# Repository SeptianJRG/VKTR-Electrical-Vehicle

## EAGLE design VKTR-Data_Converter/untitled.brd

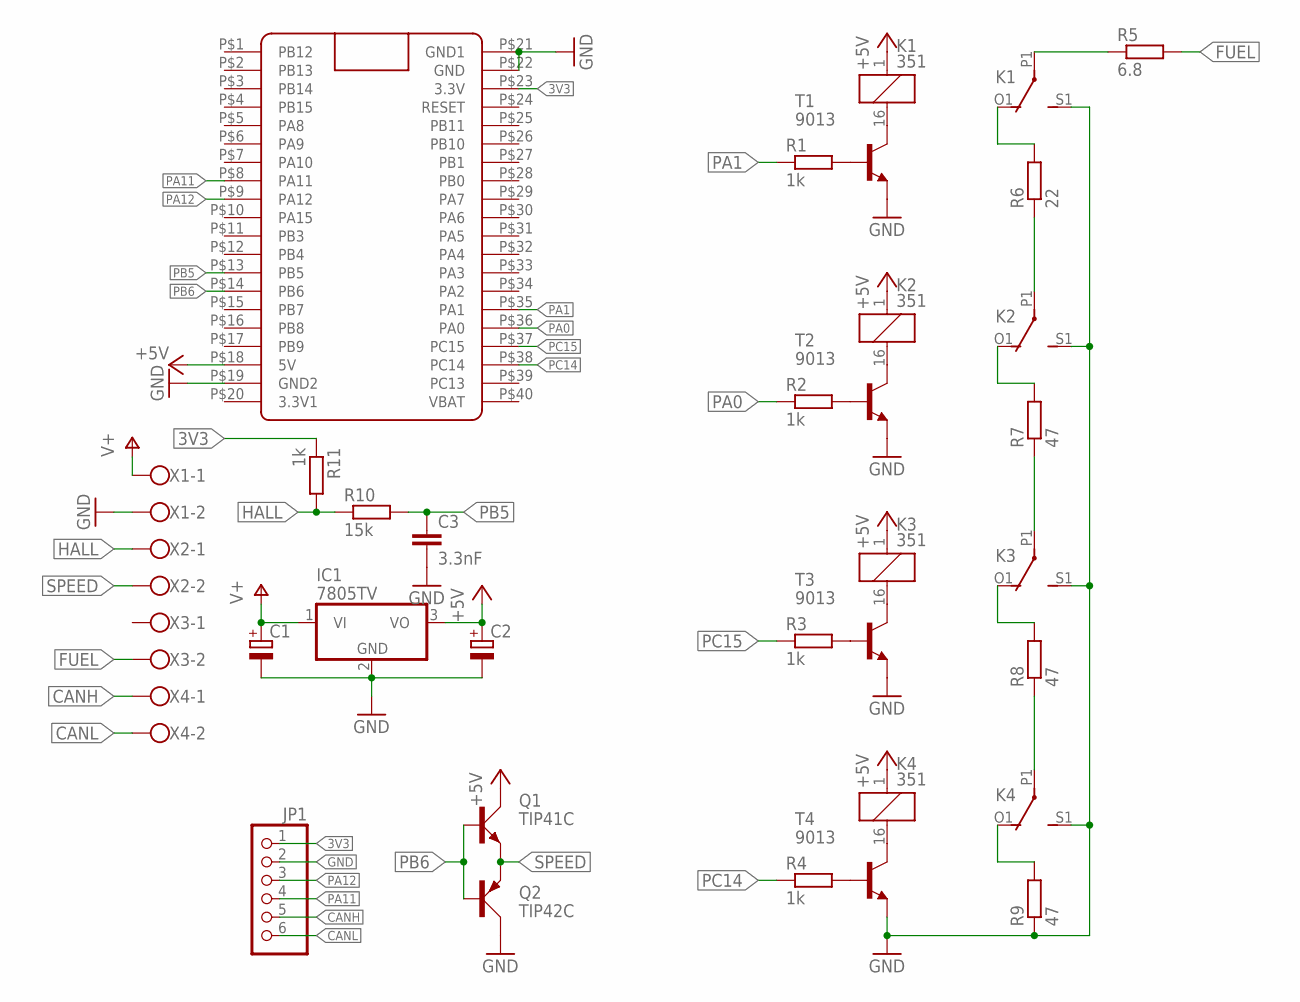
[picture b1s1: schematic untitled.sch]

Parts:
C1, C2: CPOL-EUE5-10.5; E5-10,5
C3: 3.3nF; C050-024X044
IC1: 7805TV; TO220V
JP1: PINHD-1X6; 1X06
K1, K2, K3, K4: 351
Q1: TIP41C; TO220AV
Q2: TIP42C; TO220AV
R1, R2, R3, R4, R11: 1k; 0207/7
R5: 6.8; 0207/7
R6: 22; 0207/7
R7, R8, R9: 47; 0207/7
R10: 15k; 0207/7
T1, T2, T3, T4: 9013; TO92-EBC
U$1: BLUE_PILL
X1, X2, X3, X4: W237-102

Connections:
3V3: JP1.1, R11.1, U$1.P$23 (3.3V)
+5V: C2.+, IC1.3 (VO), K1.1, K2.1, K3.1, K4.1, Q1.C, U$1.P$18 (5V)
CANH: JP1.5, X4.1
CANL: JP1.6, X4.2
FUEL: R5.2, X3.2
GND: C1.-, C2.-, C3.2, IC1.2 (GND), JP1.2, K1.S1 (S), K2.S1 (S), K3.S1 (S), K4.S1 (S), Q2.C, R9.1, T1.E, T2.E, T3.E, T4.E, U$1.P$19 (GND2), U$1.P$21 (GND1), U$1.P$22 (GND), X1.2
HALL: R10.1, R11.2, X2.1
unnamed: K1.P1, R5.1
unnamed: K1.16 (2), T1.C
unnamed: R1.2, T1.B
unnamed: K2.16 (2), T2.C
unnamed: R2.2, T2.B
unnamed: K3.16 (2), T3.C
unnamed: R3.2, T3.B
unnamed: K4.16 (2), T4.C
unnamed: R4.2, T4.B
unnamed: K2.P1, R6.1
unnamed: K1.O1 (O), R6.2
unnamed: K3.P1, R7.1
unnamed: K2.O1 (O), R7.2
unnamed: K4.P1, R8.1
unnamed: K3.O1 (O), R8.2
unnamed: K4.O1 (O), R9.2
PA0: R2.1, U$1.P$36 (PA0)
PA1: R1.1, U$1.P$35 (PA1)
PA11: JP1.4, U$1.P$8 (PA11)
PA12: JP1.3, U$1.P$9 (PA12)
PB5: C3.1, R10.2, U$1.P$13 (PB5)
PB6: Q1.B, Q2.B, U$1.P$14 (PB6)
PC14: R4.1, U$1.P$38 (PC14)
PC15: R3.1, U$1.P$37 (PC15)
SPEED: Q1.E, Q2.E, X2.2
V+: C1.+, IC1.1 (VI), X1.1

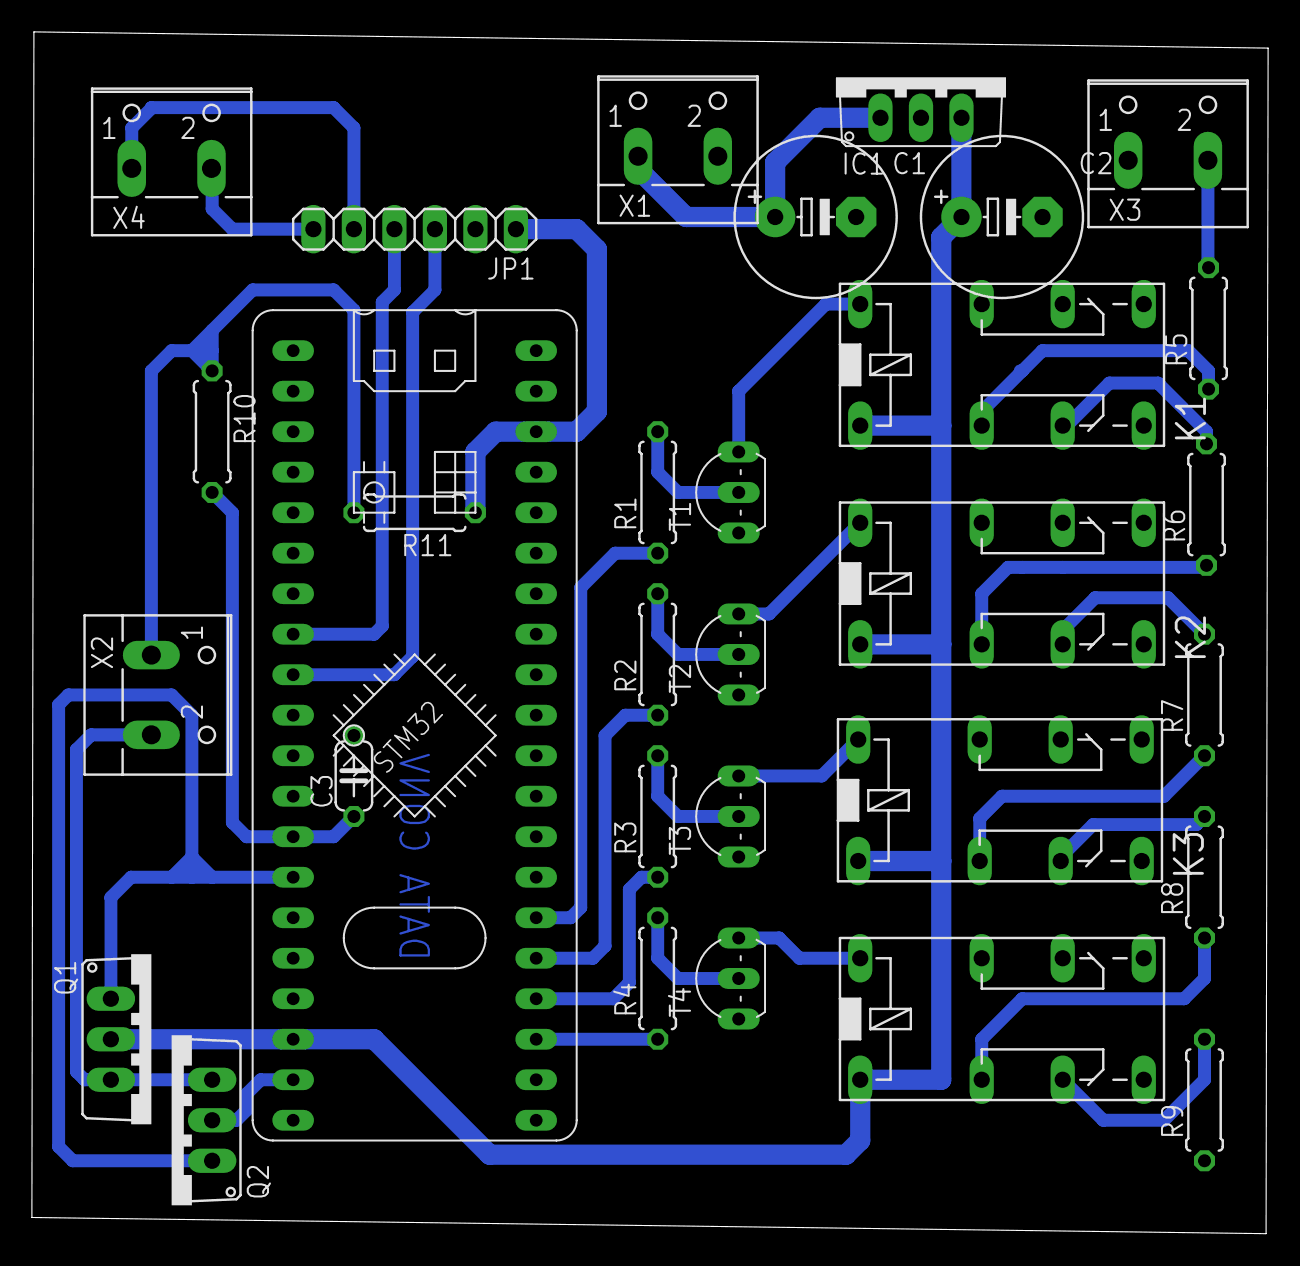
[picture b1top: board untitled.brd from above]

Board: 2 copper layers, 77.5 x 75.4 mm, 31 parts (0 on the bottom side), 33 nets.

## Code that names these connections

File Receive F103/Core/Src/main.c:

/* USER CODE BEGIN Header */
/**
  ******************************************************************************
  * @file           : main.c
  * @brief          : Main program body
  ******************************************************************************
  * @attention
  *
  * Copyright (c) 2022 STMicroelectronics.
  * All rights reserved.
  *
  * This software is licensed under terms that can be found in the LICENSE file
  * in the root directory of this software component.
  * If no LICENSE file comes with this software, it is provided AS-IS.
  *
  ******************************************************************************
  */
/* USER CODE END Header */
/* Includes ------------------------------------------------------------------*/
#include "main.h"

/* Private includes ----------------------------------------------------------*/
/* USER CODE BEGIN Includes */

/* USER CODE END Includes */

/* Private typedef -----------------------------------------------------------*/
/* USER CODE BEGIN PTD */

/* USER CODE END PTD */

/* Private define ------------------------------------------------------------*/
/* USER CODE BEGIN PD */
/* USER CODE END PD */

/* Private macro -------------------------------------------------------------*/
/* USER CODE BEGIN PM */

/* USER CODE END PM */

/* Private variables ---------------------------------------------------------*/

/* USER CODE BEGIN PV */

/* USER CODE END PV */

/* Private function prototypes -----------------------------------------------*/
void SystemClock_Config(void);
static void MX_GPIO_Init(void);
/* USER CODE BEGIN PFP */

/* USER CODE END PFP */

/* Private user code ---------------------------------------------------------*/
/* USER CODE BEGIN 0 */

/* USER CODE END 0 */

/**
  * @brief  The application entry point.
  * @retval int
  */
int main(void)
{
  /* USER CODE BEGIN 1 */

  /* USER CODE END 1 */

  /* MCU Configuration--------------------------------------------------------*/

  /* Reset of all peripherals, Initializes the Flash interface and the Systick. */
  HAL_Init();

  /* USER CODE BEGIN Init */

  /* USER CODE END Init */

  /* Configure the system clock */
  SystemClock_Config();

  /* USER CODE BEGIN SysInit */

  /* USER CODE END SysInit */

  /* Initialize all configured peripherals */
  MX_GPIO_Init();
  /* USER CODE BEGIN 2 */

  /* USER CODE END 2 */

  /* Infinite loop */
  /* USER CODE BEGIN WHILE */
  while (1)
  {
    /* USER CODE END WHILE */

    /* USER CODE BEGIN 3 */
		HAL_GPIO_WritePin(GPIOC, GPIO_PIN_14, 1);
		HAL_GPIO_WritePin(GPIOC, GPIO_PIN_15, 0);
		HAL_GPIO_WritePin(GPIOA, GPIO_PIN_0, 0);
		HAL_GPIO_WritePin(GPIOA, GPIO_PIN_1, 0);

		HAL_Delay(1000);

		HAL_GPIO_WritePin(GPIOC, GPIO_PIN_14, 0);
		HAL_GPIO_WritePin(GPIOC, GPIO_PIN_15, 1);
		HAL_GPIO_WritePin(GPIOA, GPIO_PIN_0, 0);
		HAL_GPIO_WritePin(GPIOA, GPIO_PIN_1, 0);

		HAL_Delay(1000);
		
		HAL_GPIO_WritePin(GPIOC, GPIO_PIN_14, 0);
		HAL_GPIO_WritePin(GPIOC, GPIO_PIN_15, 0);
		HAL_GPIO_WritePin(GPIOA, GPIO_PIN_0, 1);
		HAL_GPIO_WritePin(GPIOA, GPIO_PIN_1, 0);

		HAL_Delay(1000);

		HAL_GPIO_WritePin(GPIOC, GPIO_PIN_14, 0);
		HAL_GPIO_WritePin(GPIOC, GPIO_PIN_15, 0);
		HAL_GPIO_WritePin(GPIOA, GPIO_PIN_0, 0);
		HAL_GPIO_WritePin(GPIOA, GPIO_PIN_1, 1);

		HAL_Delay(1000);
  /* USER CODE END 3 */
}

/**
  * @brief System Clock Configuration
  * @retval None
  */
void SystemClock_Config(void)
{
  RCC_OscInitTypeDef RCC_OscInitStruct = {0};
  RCC_ClkInitTypeDef RCC_ClkInitStruct = {0};

  /** Initializes the RCC Oscillators according to the specified parameters
  * in the RCC_OscInitTypeDef structure.
  */
  RCC_OscInitStruct.OscillatorType = RCC_OSCILLATORTYPE_HSE;
  RCC_OscInitStruct.HSEState = RCC_HSE_ON;
  RCC_OscInitStruct.HSEPredivValue = RCC_HSE_PREDIV_DIV1;
  RCC_OscInitStruct.HSIState = RCC_HSI_ON;
  RCC_OscInitStruct.PLL.PLLState = RCC_PLL_ON;
  RCC_OscInitStruct.PLL.PLLSource = RCC_PLLSOURCE_HSE;
  RCC_OscInitStruct.PLL.PLLMUL = RCC_PLL_MUL9;
  if (HAL_RCC_OscConfig(&RCC_OscInitStruct) != HAL_OK)
  {
    Error_Handler();
  }

  /** Initializes the CPU, AHB and APB buses clocks
  */
  RCC_ClkInitStruct.ClockType = RCC_CLOCKTYPE_HCLK|RCC_CLOCKTYPE_SYSCLK
                              |RCC_CLOCKTYPE_PCLK1|RCC_CLOCKTYPE_PCLK2;
  RCC_ClkInitStruct.SYSCLKSource = RCC_SYSCLKSOURCE_PLLCLK;
  RCC_ClkInitStruct.AHBCLKDivider = RCC_SYSCLK_DIV1;
  RCC_ClkInitStruct.APB1CLKDivider = RCC_HCLK_DIV2;
  RCC_ClkInitStruct.APB2CLKDivider = RCC_HCLK_DIV1;

  if (HAL_RCC_ClockConfig(&RCC_ClkInitStruct, FLASH_LATENCY_2) != HAL_OK)
  {
    Error_Handler();
  }
}

/**
  * @brief GPIO Initialization Function
  * @param None
  * @retval None
  */
static void MX_GPIO_Init(void)
{
  GPIO_InitTypeDef GPIO_InitStruct = {0};

  /* GPIO Ports Clock Enable */
  __HAL_RCC_GPIOC_CLK_ENABLE();
  __HAL_RCC_GPIOD_CLK_ENABLE();
  __HAL_RCC_GPIOA_CLK_ENABLE();

  /*Configure GPIO pin Output Level */
  HAL_GPIO_WritePin(GPIOC, GPIO_PIN_14|GPIO_PIN_15, GPIO_PIN_RESET);

  /*Configure GPIO pin Output Level */
  HAL_GPIO_WritePin(GPIOA, GPIO_PIN_0|GPIO_PIN_1, GPIO_PIN_RESET);

  /*Configure GPIO pins : PC14 PC15 */
  GPIO_InitStruct.Pin = GPIO_PIN_14|GPIO_PIN_15;
  GPIO_InitStruct.Mode = GPIO_MODE_OUTPUT_PP;
  GPIO_InitStruct.Pull = GPIO_NOPULL;
  GPIO_InitStruct.Speed = GPIO_SPEED_FREQ_LOW;
  HAL_GPIO_Init(GPIOC, &GPIO_InitStruct);

  /*Configure GPIO pins : PA0 PA1 */
  GPIO_InitStruct.Pin = GPIO_PIN_0|GPIO_PIN_1;
  GPIO_InitStruct.Mode = GPIO_MODE_OUTPUT_PP;
  GPIO_InitStruct.Pull = GPIO_NOPULL;
  GPIO_InitStruct.Speed = GPIO_SPEED_FREQ_LOW;
  HAL_GPIO_Init(GPIOA, &GPIO_InitStruct);

}

/* USER CODE BEGIN 4 */

/* USER CODE END 4 */

/**
  * @brief  This function is executed in case of error occurrence.
  * @retval None
  */
void Error_Handler(void)
{
  /* USER CODE BEGIN Error_Handler_Debug */
  /* User can add his own implementation to report the HAL error return state */
  __disable_irq();
  while (1)
  {
  }
  /* USER CODE END Error_Handler_Debug */
}

#ifdef  USE_FULL_ASSERT
/**
  * @brief  Reports the name of the source file and the source line number
  *         where the assert_param error has occurred.
  * @param  file: pointer to the source file name
  * @param  line: assert_param error line source number
  * @retval None
  */
void assert_failed(uint8_t *file, uint32_t line)
{
  /* USER CODE BEGIN 6 */
  /* User can add his own implementation to report the file name and line number,
     ex: printf("Wrong parameters value: file %s on line %d\r\n", file, line) */
  /* USER CODE END 6 */
}
#endif /* USE_FULL_ASSERT */

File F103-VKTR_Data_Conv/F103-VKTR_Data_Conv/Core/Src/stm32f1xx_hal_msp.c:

/* USER CODE BEGIN Header */
/**
  ******************************************************************************
  * @file         stm32f1xx_hal_msp.c
  * @brief        This file provides code for the MSP Initialization
  *               and de-Initialization codes.
  ******************************************************************************
  * @attention
  *
  * Copyright (c) 2022 STMicroelectronics.
  * All rights reserved.
  *
  * This software is licensed under terms that can be found in the LICENSE file
  * in the root directory of this software component.
  * If no LICENSE file comes with this software, it is provided AS-IS.
  *
  ******************************************************************************
  */
/* USER CODE END Header */

/* Includes ------------------------------------------------------------------*/
#include "main.h"
/* USER CODE BEGIN Includes */

/* USER CODE END Includes */

/* Private typedef -----------------------------------------------------------*/
/* USER CODE BEGIN TD */

/* USER CODE END TD */

/* Private define ------------------------------------------------------------*/
/* USER CODE BEGIN Define */

/* USER CODE END Define */

/* Private macro -------------------------------------------------------------*/
/* USER CODE BEGIN Macro */

/* USER CODE END Macro */

/* Private variables ---------------------------------------------------------*/
/* USER CODE BEGIN PV */

/* USER CODE END PV */

/* Private function prototypes -----------------------------------------------*/
/* USER CODE BEGIN PFP */

/* USER CODE END PFP */

/* External functions --------------------------------------------------------*/
/* USER CODE BEGIN ExternalFunctions */

/* USER CODE END ExternalFunctions */

/* USER CODE BEGIN 0 */

/* USER CODE END 0 */

void HAL_TIM_MspPostInit(TIM_HandleTypeDef *htim);
                    /**
  * Initializes the Global MSP.
  */
void HAL_MspInit(void)
{
  /* USER CODE BEGIN MspInit 0 */

  /* USER CODE END MspInit 0 */

  __HAL_RCC_AFIO_CLK_ENABLE();
  __HAL_RCC_PWR_CLK_ENABLE();

  /* System interrupt init*/

  /** NOJTAG: JTAG-DP Disabled and SW-DP Enabled
  */
  __HAL_AFIO_REMAP_SWJ_NOJTAG();

  /* USER CODE BEGIN MspInit 1 */

  /* USER CODE END MspInit 1 */
}

/**
* @brief CAN MSP Initialization
* This function configures the hardware resources used in this example
* @param hcan: CAN handle pointer
* @retval None
*/
void HAL_CAN_MspInit(CAN_HandleTypeDef* hcan)
{
  GPIO_InitTypeDef GPIO_InitStruct = {0};
  if(hcan->Instance==CAN1)
  {
  /* USER CODE BEGIN CAN1_MspInit 0 */

  /* USER CODE END CAN1_MspInit 0 */
    /* Peripheral clock enable */
    __HAL_RCC_CAN1_CLK_ENABLE();

    __HAL_RCC_GPIOA_CLK_ENABLE();
    /**CAN GPIO Configuration
    PA11     ------> CAN_RX
    PA12     ------> CAN_TX
    */
    GPIO_InitStruct.Pin = GPIO_PIN_11;
    GPIO_InitStruct.Mode = GPIO_MODE_INPUT;
    GPIO_InitStruct.Pull = GPIO_NOPULL;
    HAL_GPIO_Init(GPIOA, &GPIO_InitStruct);

    GPIO_InitStruct.Pin = GPIO_PIN_12;
    GPIO_InitStruct.Mode = GPIO_MODE_AF_PP;
    GPIO_InitStruct.Speed = GPIO_SPEED_FREQ_HIGH;
    HAL_GPIO_Init(GPIOA, &GPIO_InitStruct);

    /* CAN1 interrupt Init */
    HAL_NVIC_SetPriority(CAN1_RX1_IRQn, 0, 0);
    HAL_NVIC_EnableIRQ(CAN1_RX1_IRQn);
  /* USER CODE BEGIN CAN1_MspInit 1 */

  /* USER CODE END CAN1_MspInit 1 */
  }

}

/**
* @brief CAN MSP De-Initialization
* This function freeze the hardware resources used in this example
* @param hcan: CAN handle pointer
* @retval None
*/
void HAL_CAN_MspDeInit(CAN_HandleTypeDef* hcan)
{
  if(hcan->Instance==CAN1)
  {
  /* USER CODE BEGIN CAN1_MspDeInit 0 */

  /* USER CODE END CAN1_MspDeInit 0 */
    /* Peripheral clock disable */
    __HAL_RCC_CAN1_CLK_DISABLE();

    /**CAN GPIO Configuration
    PA11     ------> CAN_RX
    PA12     ------> CAN_TX
    */
    HAL_GPIO_DeInit(GPIOA, GPIO_PIN_11|GPIO_PIN_12);

    /* CAN1 interrupt DeInit */
    HAL_NVIC_DisableIRQ(CAN1_RX1_IRQn);
  /* USER CODE BEGIN CAN1_MspDeInit 1 */

  /* USER CODE END CAN1_MspDeInit 1 */
  }

}

/**
* @brief TIM_PWM MSP Initialization
* This function configures the hardware resources used in this example
* @param htim_pwm: TIM_PWM handle pointer
* @retval None
*/
void HAL_TIM_PWM_MspInit(TIM_HandleTypeDef* htim_pwm)
{
  if(htim_pwm->Instance==TIM2)
  {
  /* USER CODE BEGIN TIM2_MspInit 0 */

  /* USER CODE END TIM2_MspInit 0 */
    /* Peripheral clock enable */
    __HAL_RCC_TIM2_CLK_ENABLE();
    /* TIM2 interrupt Init */
    HAL_NVIC_SetPriority(TIM2_IRQn, 0, 0);
    HAL_NVIC_EnableIRQ(TIM2_IRQn);
  /* USER CODE BEGIN TIM2_MspInit 1 */

  /* USER CODE END TIM2_MspInit 1 */
  }
  else if(htim_pwm->Instance==TIM4)
  {
  /* USER CODE BEGIN TIM4_MspInit 0 */

  /* USER CODE END TIM4_MspInit 0 */
    /* Peripheral clock enable */
    __HAL_RCC_TIM4_CLK_ENABLE();
  /* USER CODE BEGIN TIM4_MspInit 1 */

  /* USER CODE END TIM4_MspInit 1 */
  }

}

void HAL_TIM_MspPostInit(TIM_HandleTypeDef* htim)
{
  GPIO_InitTypeDef GPIO_InitStruct = {0};
  if(htim->Instance==TIM4)
  {
  /* USER CODE BEGIN TIM4_MspPostInit 0 */

  /* USER CODE END TIM4_MspPostInit 0 */

    __HAL_RCC_GPIOB_CLK_ENABLE();
    /**TIM4 GPIO Configuration
    PB6     ------> TIM4_CH1
    */
    GPIO_InitStruct.Pin = GPIO_PIN_6;
    GPIO_InitStruct.Mode = GPIO_MODE_AF_PP;
    GPIO_InitStruct.Speed = GPIO_SPEED_FREQ_LOW;
    HAL_GPIO_Init(GPIOB, &GPIO_InitStruct);

  /* USER CODE BEGIN TIM4_MspPostInit 1 */

  /* USER CODE END TIM4_MspPostInit 1 */
  }

}
/**
* @brief TIM_PWM MSP De-Initialization
* This function freeze the hardware resources used in this example
* @param htim_pwm: TIM_PWM handle pointer
* @retval None
*/
void HAL_TIM_PWM_MspDeInit(TIM_HandleTypeDef* htim_pwm)
{
  if(htim_pwm->Instance==TIM2)
  {
  /* USER CODE BEGIN TIM2_MspDeInit 0 */

  /* USER CODE END TIM2_MspDeInit 0 */
    /* Peripheral clock disable */
    __HAL_RCC_TIM2_CLK_DISABLE();

    /* TIM2 interrupt DeInit */
    HAL_NVIC_DisableIRQ(TIM2_IRQn);
  /* USER CODE BEGIN TIM2_MspDeInit 1 */

  /* USER CODE END TIM2_MspDeInit 1 */
  }
  else if(htim_pwm->Instance==TIM4)
  {
  /* USER CODE BEGIN TIM4_MspDeInit 0 */

  /* USER CODE END TIM4_MspDeInit 0 */
    /* Peripheral clock disable */
    __HAL_RCC_TIM4_CLK_DISABLE();
  /* USER CODE BEGIN TIM4_MspDeInit 1 */

  /* USER CODE END TIM4_MspDeInit 1 */
  }

}

/* USER CODE BEGIN 1 */

/* USER CODE END 1 */
